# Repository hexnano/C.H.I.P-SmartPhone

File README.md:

# C.H.I.P-SmartPhone
Open Source SmartPhone

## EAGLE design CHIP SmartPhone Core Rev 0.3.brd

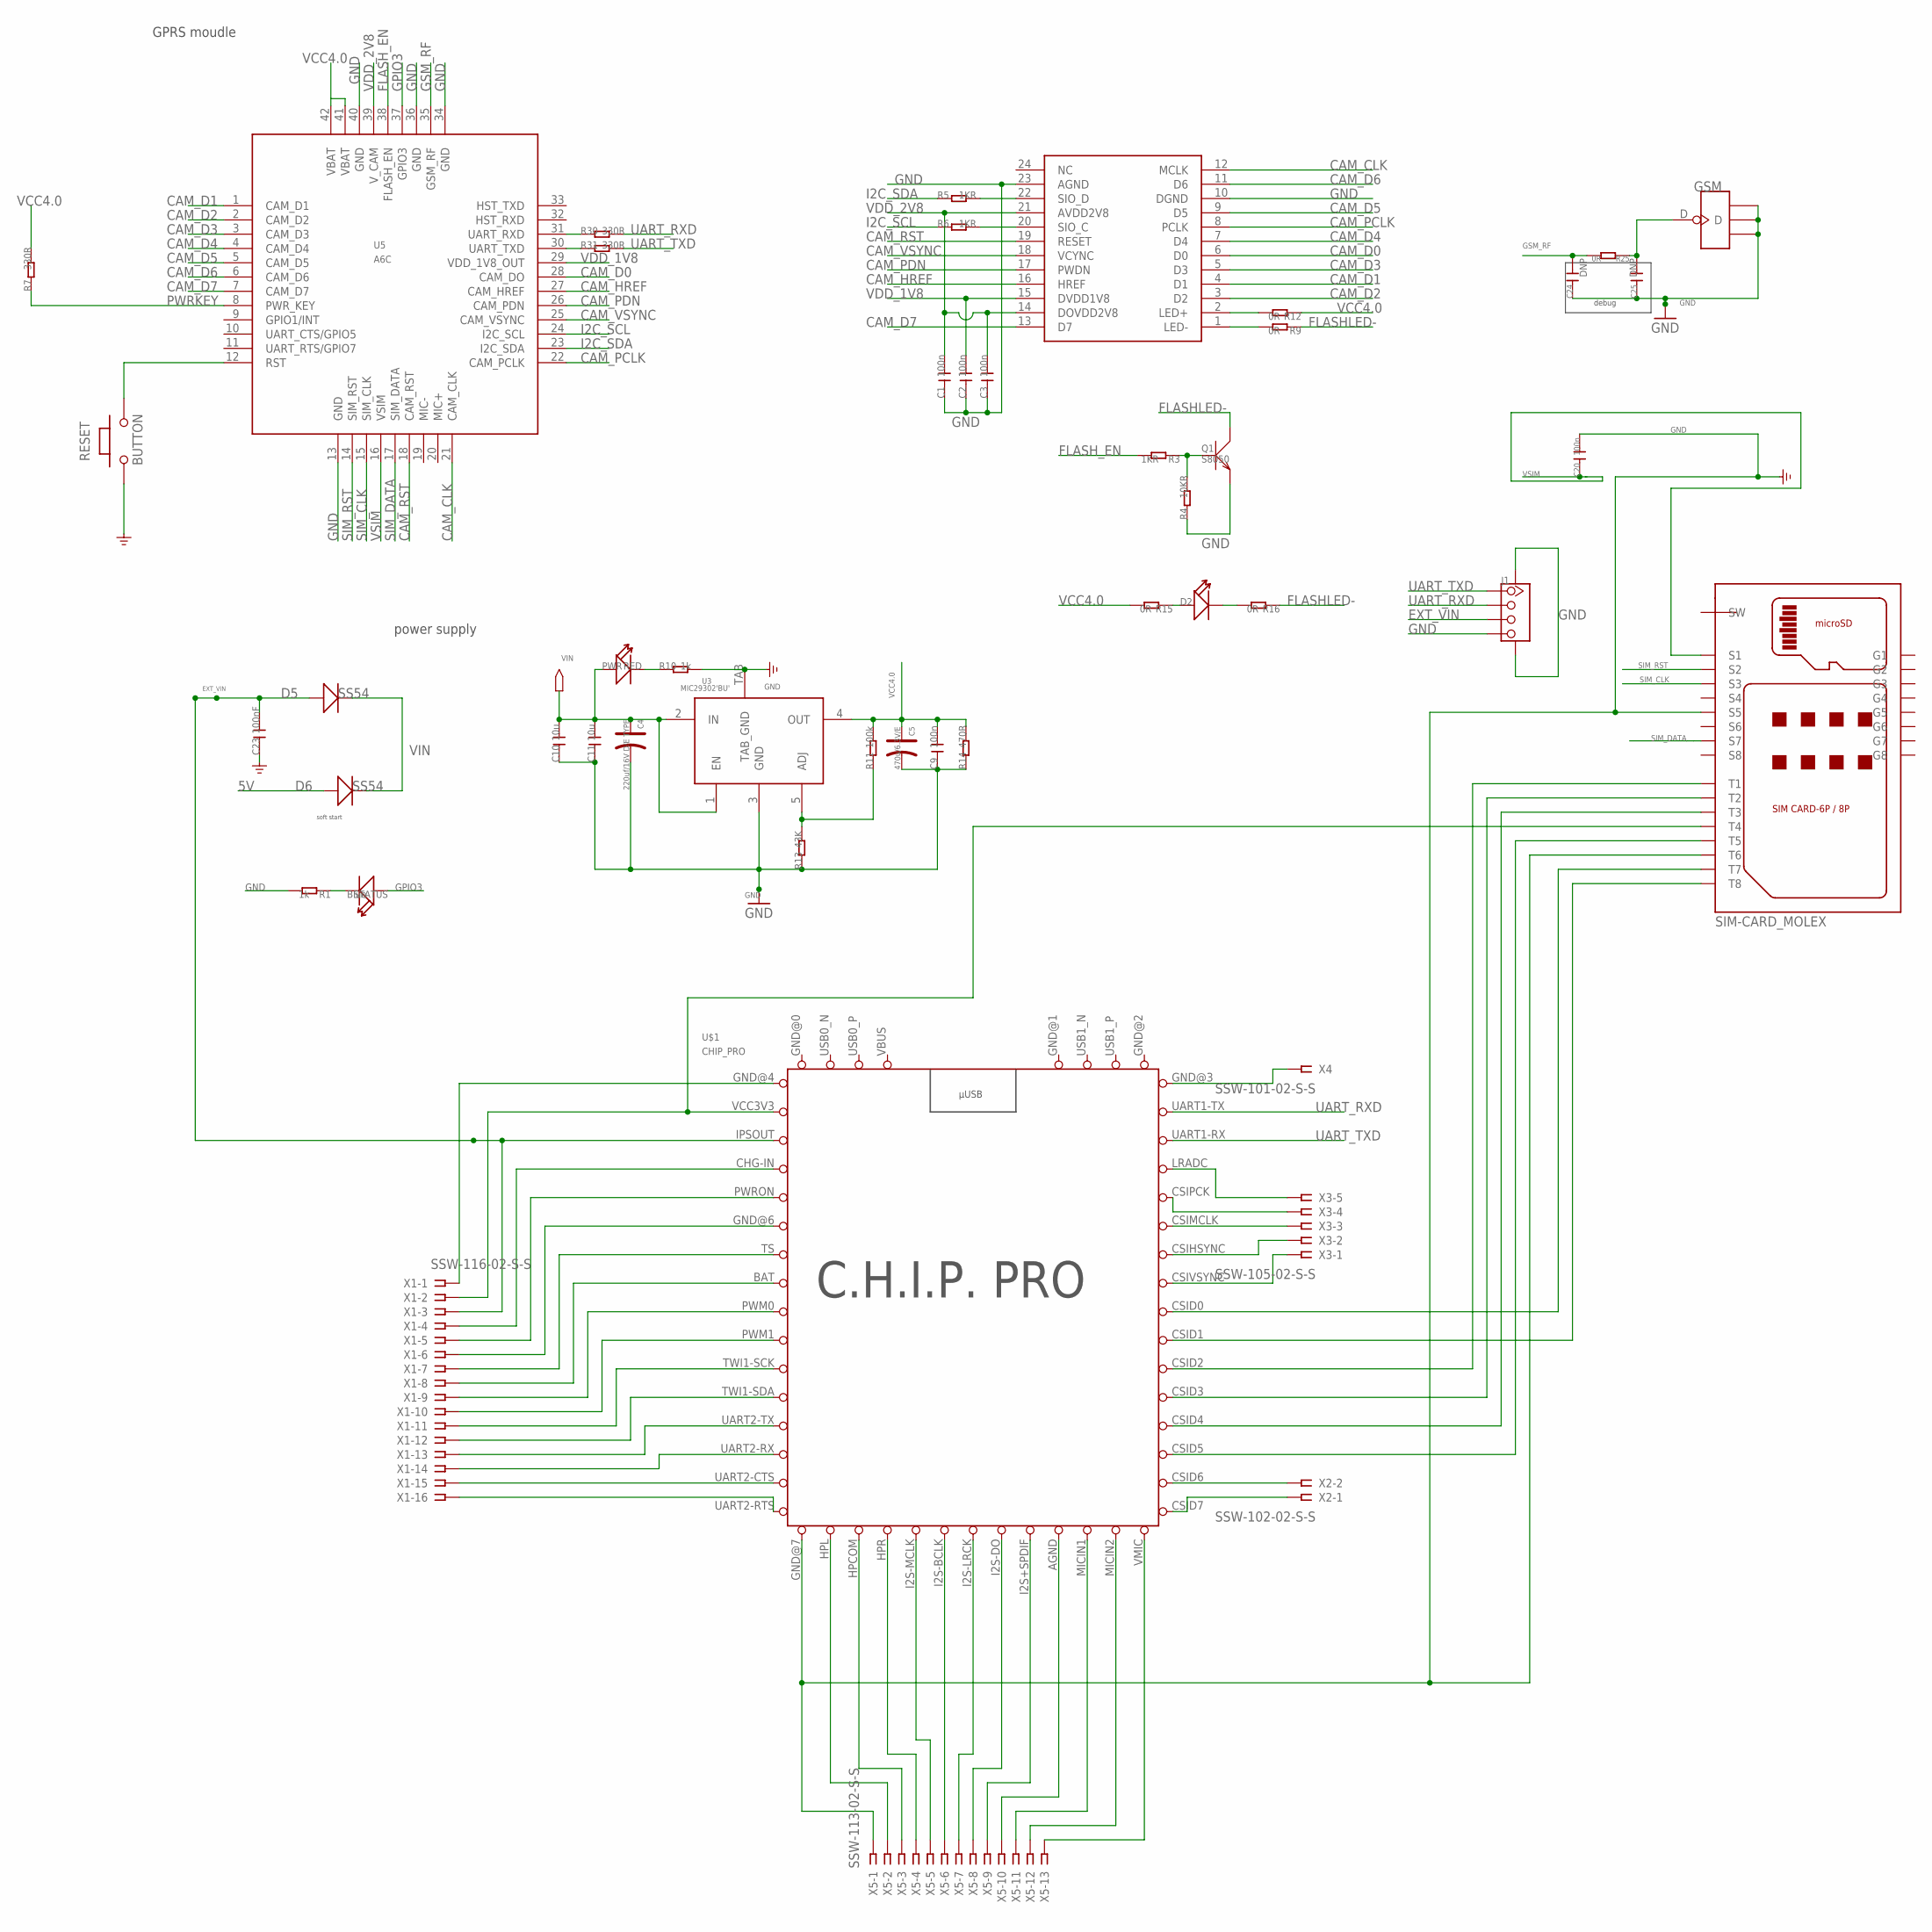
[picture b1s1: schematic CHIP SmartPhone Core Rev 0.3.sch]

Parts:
C1, C2, C3, C9, C20: 100n; C0603
C4: 220uf/16V D/E TYPE; AVX_D
C5: 470u/6.3V/E; AVX_D
C10, C11: 10u; C0603
C23: 100nF; C0603
C24, C25: DNP; C0402
D2: LED'0805'; LED-0805
D5, D6: SS54; SMB
GSM: ANTENNA-U-FL; 4P-U-FL
J1: TWIG-4P-2.0-SMD-FEMALE-REINFORCE'90D'; 4P-SMD-2.0-90D
PWR: RED; D0603
Q1: S8050; SOT23
R1, R10: 1k; R0603
R3, R5, R6: 1KR; R0603
R4: 10KR; R0603
R7, R30, R31: 330R; R0603
R9, R12, R15, R16: 0R; R0603
R11: 100k; R0603
R13: 43K; R0603
R14: 470R; R0603
R25: 0R; R0402
RESET: BUTTON; 157SW
STATUS: Blue; D0603
U1: FPC-SOCKET-0.5-24P; 24P-0.5-90D
U3: MIC29302'BU'; TO-263
U5: A6C
U$1: CHIP_PRO
U$4: SIM-CARD_MOLEX
X1: SSW-116-02-S-S
X2: SSW-102-02-S-S
X3: SSW-105-02-S-S
X4: SSW-101-02-S-S
X5: SSW-113-02-S-S

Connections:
5V: D6.+
CAM_CLK: U1.12 (MCLK), U5.21 (CAM_CLK)
CAM_D0: U1.6 (D0), U5.28 (CAM_DO)
CAM_D1: U1.4 (D1), U5.1 (CAM_D1)
CAM_D2: U1.3 (D2), U5.2 (CAM_D2)
CAM_D3: U1.5 (D3), U5.3 (CAM_D3)
CAM_D4: U1.7 (D4), U5.4 (CAM_D4)
CAM_D5: U1.9 (D5), U5.5 (CAM_D5)
CAM_D6: U1.11 (D6), U5.6 (CAM_D6)
CAM_D7: U1.13 (D7), U5.7 (CAM_D7)
CAM_HREF: U1.16 (HREF), U5.27 (CAM_HREF)
CAM_PCLK: U1.8 (PCLK), U5.22 (CAM_PCLK)
CAM_PDN: U1.17 (PWDN), U5.26 (CAM_PDN)
CAM_RST: U1.19 (RESET), U5.18 (CAM_RST)
CAM_VSYNC: U1.18 (VCYNC), U5.25 (CAM_VSYNC)
EXT_VIN: C23.2, D5.+, J1.3, U$1.IPSOUT, X1.3
FLASHLED-: Q1.3 (C), R9.1, R16.1
FLASH_EN: R3.2, U5.38 (FLASH_EN)
GND: C1.1, C2.1, C3.1, C4.-, C5.-, C9.1, C10.1, C11.1, C20.2, C23.1, C24.1, C25.1, GSM.GND1, GSM.GND2, GSM.GND3, J1.4, J1.SS1, J1.SS2, Q1.2 (E), R1.2, R4.1, R10.2, R13.1, R14.1, RESET.1, U1.10 (DGND), U1.23 (AGND), U3.3 (GND), U3.TAB (TAB_GND), U5.13 (GND), U5.34 (GND), U5.36 (GND), U5.40 (GND), U$1.GND@0 (GND), U$1.GND@1 (GND), U$1.GND@2 (GND), U$1.GND@7 (GND), U$4.S5, U$4.T6, X5.1
GPIO3: STATUS.+, U5.37 (GPIO3)
GSM_RF: C24.2, R25.2, U5.35 (GSM_RF)
I2C_SCL: R6.1, U5.24 (I2C_SCL)
I2C_SDA: R5.1, U5.23 (I2C_SDA)
unnamed: R1.1, STATUS.-
unnamed: R30.1, U5.31 (UART_RXD)
unnamed: Q1.1 (B), R3.1, R4.2
unnamed: R31.1, U5.30 (UART_TXD)
unnamed: R11.1, R13.2, U3.5 (ADJ)
unnamed: D2.+, R15.1
unnamed: RESET.2, U5.12 (RST)
unnamed: R5.2, U1.22 (SIO_D)
unnamed: D2.-, R16.2
unnamed: R6.2, U1.20 (SIO_C)
unnamed: U$1.CSID2, U$4.T1
unnamed: U$1.CSID3, U$4.T2
unnamed: U$1.CSID4, U$4.T3
unnamed: U$1.CSID5, U$4.T5
unnamed: U$1.UART2-RTS, X1.16
unnamed: U$1.VCC3V3, U$4.T4, X1.2
unnamed: U$1.CSID0, U$4.T7
unnamed: U$1.CSID1, U$4.T8
unnamed: PWR.-, R10.1
unnamed: R9.2, U1.1 (LED-)
unnamed: R12.2, U1.2 (LED+)
unnamed: U$1.UART2-CTS, X1.15
unnamed: U$1.UART2-RX, X1.14
unnamed: U$1.UART2-TX, X1.13
unnamed: C25.2, GSM.D, R25.1
unnamed: U$1.TWI1-SDA, X1.12
unnamed: U$1.TWI1-SCK, X1.11
unnamed: U$1.PWM1, X1.10
unnamed: U$1.PWM0, X1.9
unnamed: U$1.BAT, X1.8
unnamed: U$1.TS, X1.7
unnamed: U$1.GND@6 (GND), X1.6
unnamed: U$1.PWRON, X1.5
unnamed: U$1.CHG-IN, X1.4
unnamed: U$1.GND@3 (GND), X4.1
unnamed: U$1.GND@4 (GND), X1.1
unnamed: U$1.CSIVSYNC, X3.1
unnamed: U$1.CSIHSYNC, X3.2
unnamed: U$1.CSIMCLK, X3.3
unnamed: U$1.CSIPCK, X3.4
unnamed: U$1.LRADC, X3.5
unnamed: U$1.CSID6, X2.2
unnamed: U$1.CSID7, X2.1
unnamed: U$1.VMIC, X5.13
unnamed: U$1.MICIN2, X5.12
unnamed: U$1.MICIN1, X5.11
unnamed: U$1.AGND, X5.10
unnamed: U$1.I2S+SPDIF (I2SSPDIF), X5.9
unnamed: U$1.I2S-DO (I2SDO), X5.8
unnamed: U$1.I2S-LRCK (I2SLRCK), X5.7
unnamed: U$1.I2S-BCLK (I2SBCLK), X5.6
unnamed: U$1.I2S-MCLK (I2SMCLK), X5.5
unnamed: U$1.HPR, X5.4
unnamed: U$1.HPCOM, X5.3
unnamed: U$1.HPL, X5.2
PWRKEY: R7.1, U5.8 (PWR_KEY)
SIM_CLK: U5.15 (SIM_CLK), U$4.S3
SIM_DATA: U5.17 (SIM_DATA), U$4.S7
SIM_RST: U5.14 (SIM_RST), U$4.S2
UART_RXD: J1.2, R30.2, U$1.UART1-TX
UART_TXD: J1.1, R31.2, U$1.UART1-RX
VBUS: U$1.VBUS
VCC4.0: C5.+, C9.2, R7.2, R11.2, R12.1, R14.2, R15.2, U3.4 (OUT), U5.41 (VBAT), U5.42 (VBAT)
VDD_1V8: C2.2, U1.15 (DVDD1V8), U5.29 (VDD_1V8_OUT)
VDD_2V8: C1.2, C3.2, U1.14 (DOVDD2V8), U1.21 (AVDD2V8), U5.39 (V_CAM)
VIN: C4.+, C10.2, C11.2, D5.-, D6.-, PWR.+, U3.1 (EN), U3.2 (IN)
VSIM: C20.1, U5.16 (VSIM), U$4.S1

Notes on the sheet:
GPRS moudle
debug
power supply
soft start

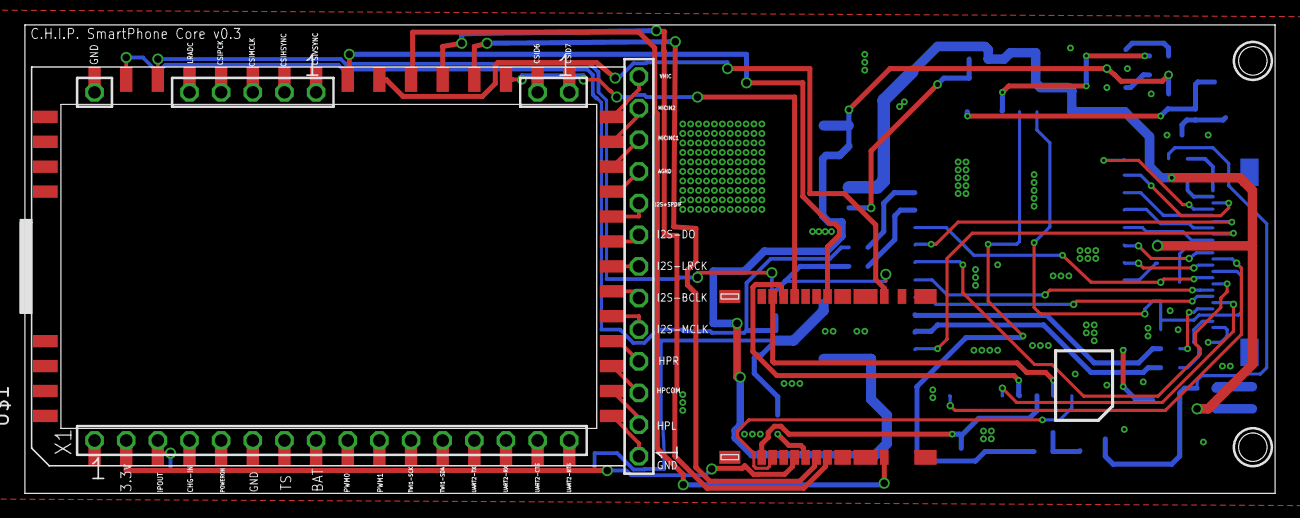
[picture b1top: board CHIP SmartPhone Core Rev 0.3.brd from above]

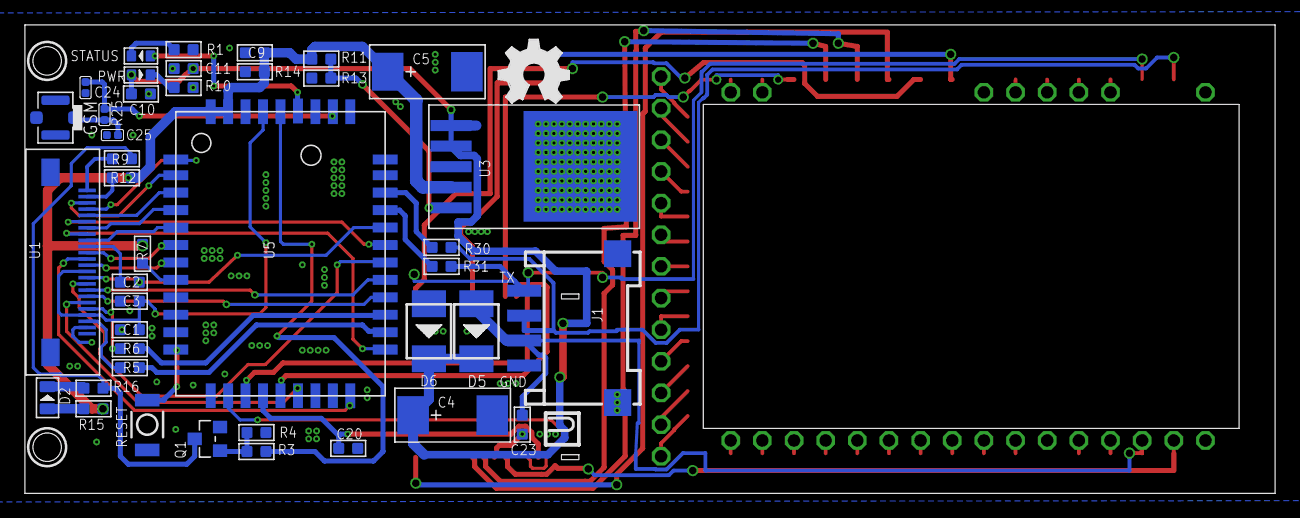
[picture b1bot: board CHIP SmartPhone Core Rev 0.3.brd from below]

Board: 2 copper layers, 100.3 x 37.6 mm, 49 parts (42 on the bottom side), 88 nets.

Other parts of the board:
LOGO2: LOGO-OSHW-FILLX0200-NT; OSHW_FILLX200_NOTEXT
